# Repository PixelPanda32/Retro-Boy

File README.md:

# Retro-Boy
A retro Emulator for Half life using a ESP32 S3 so I can play games in a little handheld device.<br>

<br>This is the pcb hopefully idk if it will work im gonna order the components and bread board it to test if it works

<br>Heres the schematic for the pcb.
I might change this to a Wroom chip if i need more time working on the project.

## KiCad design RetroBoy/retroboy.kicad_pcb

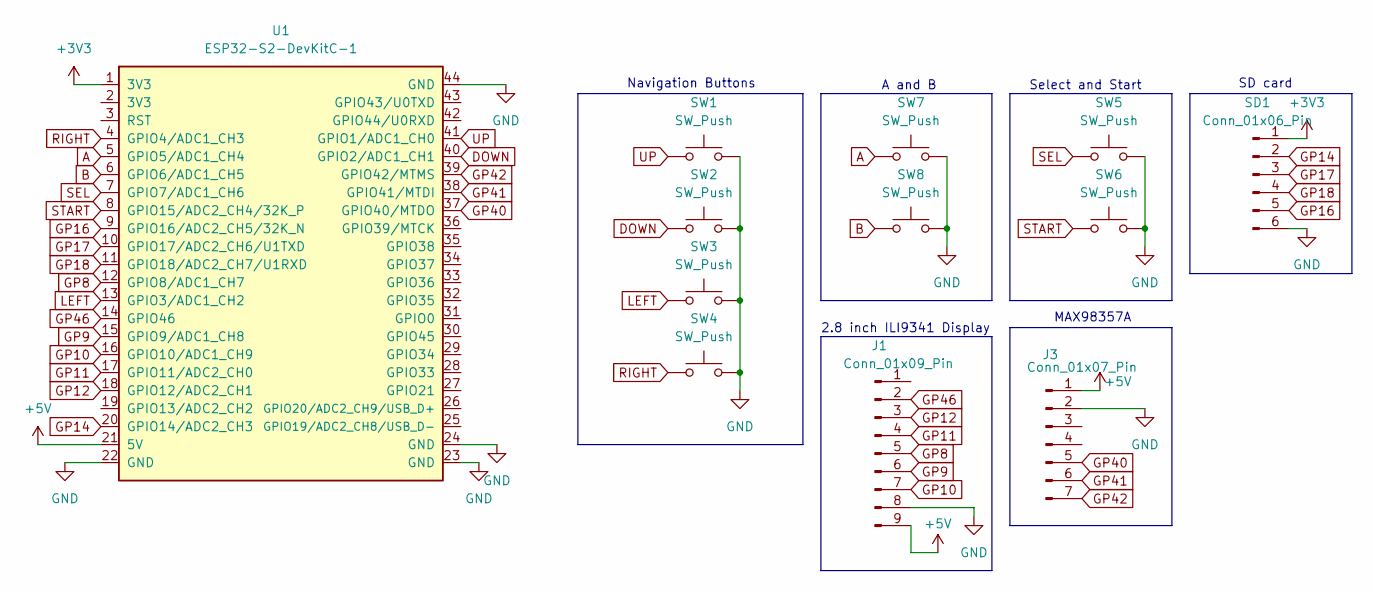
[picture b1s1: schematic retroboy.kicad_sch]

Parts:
J1: Conn_01x09_Pin; PinHeader_1x09_P2.54mm_Vertical
J3: Conn_01x07_Pin; PinHeader_1x07_P2.54mm_Vertical
SD1: Conn_01x06_Pin; PinHeader_1x06_P2.54mm_Vertical
SW1, SW2, SW3, SW4, SW5, SW6, SW7, SW8: SW_Push; SW_PUSH-12mm
U1: ESP32-S2-DevKitC-1

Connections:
+3V3: SD1.1, U1.1 (3V3)
+5V: J1.9, J3.1, U1.21 (5V)
A: SW7.1, U1.5 (GPIO5/ADC1_CH4)
B: SW8.1, U1.6 (GPIO6/ADC1_CH5)
DOWN: SW2.1, U1.40 (GPIO2/ADC1_CH1)
GND: J1.8, J3.2, SD1.6, SW1.2, SW2.2, SW3.2, SW4.2, SW5.2, SW6.2, SW7.2, SW8.2, U1.22 (GND), U1.23 (GND), U1.24 (GND), U1.44 (GND)
GP8: J1.5, U1.12 (GPIO8/ADC1_CH7)
GP9: J1.6, U1.15 (GPIO9/ADC1_CH8)
GP10: J1.7, U1.16 (GPIO10/ADC1_CH9)
GP11: J1.4, U1.17 (GPIO11/ADC2_CH0)
GP12: J1.3, U1.18 (GPIO12/ADC2_CH1)
GP14: SD1.2, U1.20 (GPIO14/ADC2_CH3)
GP16: SD1.5, U1.9 (GPIO16/ADC2_CH5/32K_N)
GP17: SD1.3, U1.10 (GPIO17/ADC2_CH6/U1TXD)
GP18: SD1.4, U1.11 (GPIO18/ADC2_CH7/U1RXD)
GP40: J3.5, U1.37 (GPIO40/MTDO)
GP41: J3.6, U1.38 (GPIO41/MTDI)
GP42: J3.7, U1.39 (GPIO42/MTMS)
GP46: J1.2, U1.14 (GPIO46)
LEFT: SW3.1, U1.13 (GPIO3/ADC1_CH2)
RIGHT: SW4.1, U1.4 (GPIO4/ADC1_CH3)
SEL: SW5.1, U1.7 (GPIO7/ADC1_CH6)
START: SW6.1, U1.8 (GPIO15/ADC2_CH4/32K_P)
UP: SW1.1, U1.41 (GPIO1/ADC1_CH0)

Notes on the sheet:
A and B
Navigation Buttons
SD card
MAX98357A
Select and Start
2.8 inch ILI9341 Display

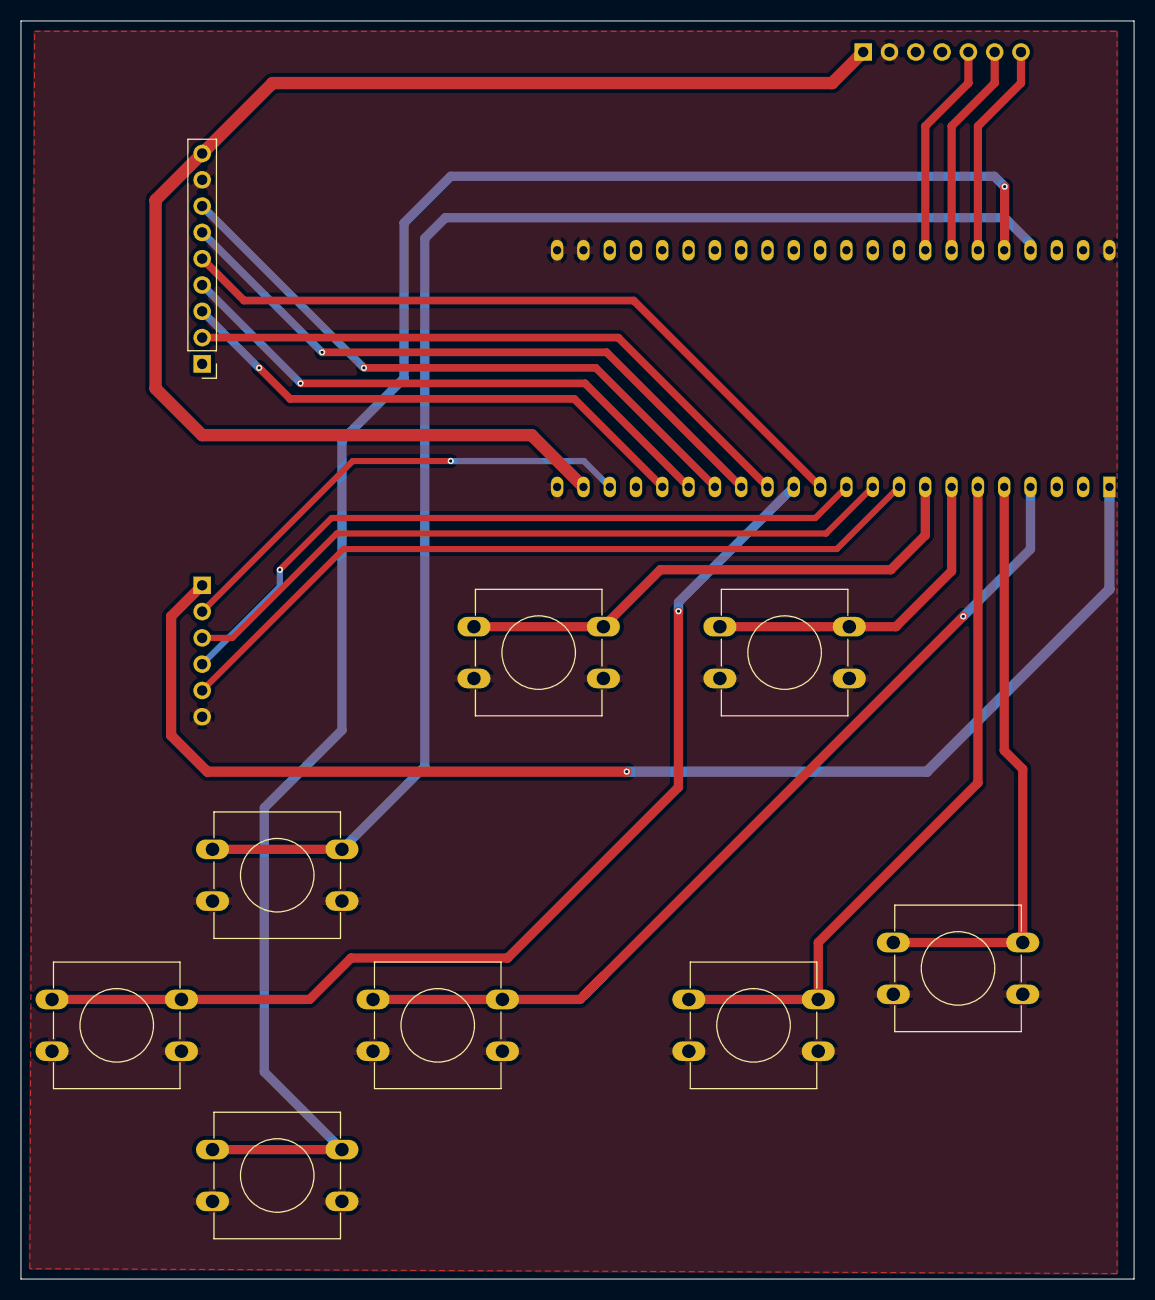
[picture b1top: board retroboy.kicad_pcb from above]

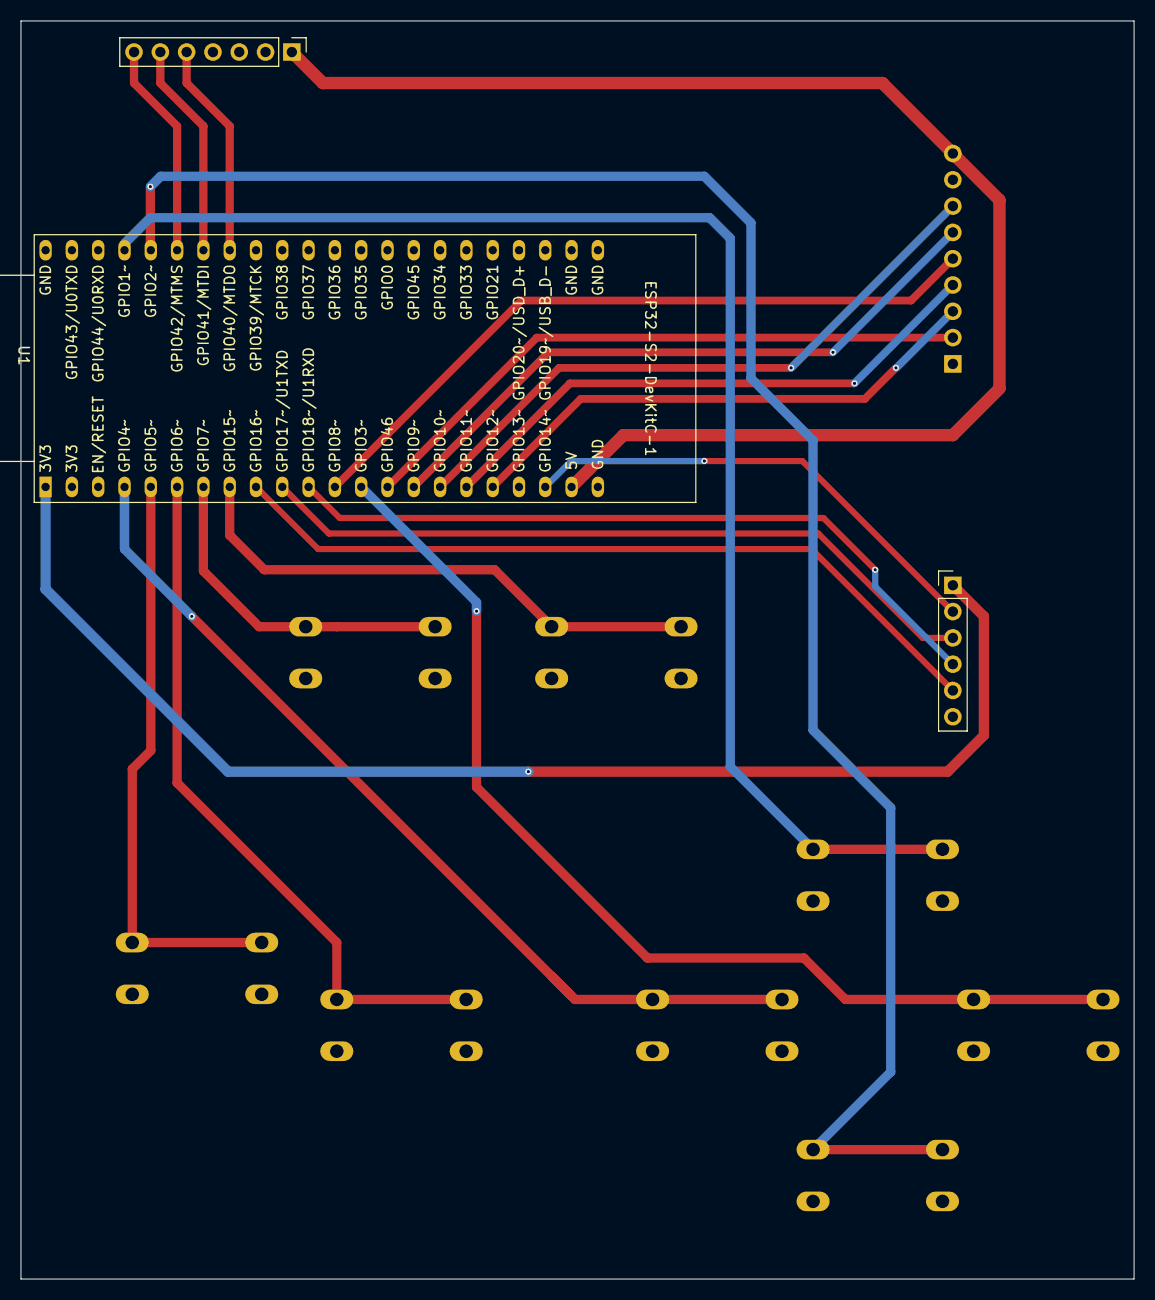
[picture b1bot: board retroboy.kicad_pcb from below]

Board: 2 copper layers, 107.5 x 121.5 mm, 12 parts (3 on the bottom side), 24 nets.
